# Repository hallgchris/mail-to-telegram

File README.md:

# Mail to Telegram

Idea: Reed switch detects mail entering letterbox. Notify family group chat via Telegram.

Result: Excuse to make a PCB and fiddle with the ESP32 module.

> 🎶 *We just got a letter, we just got a letter...*

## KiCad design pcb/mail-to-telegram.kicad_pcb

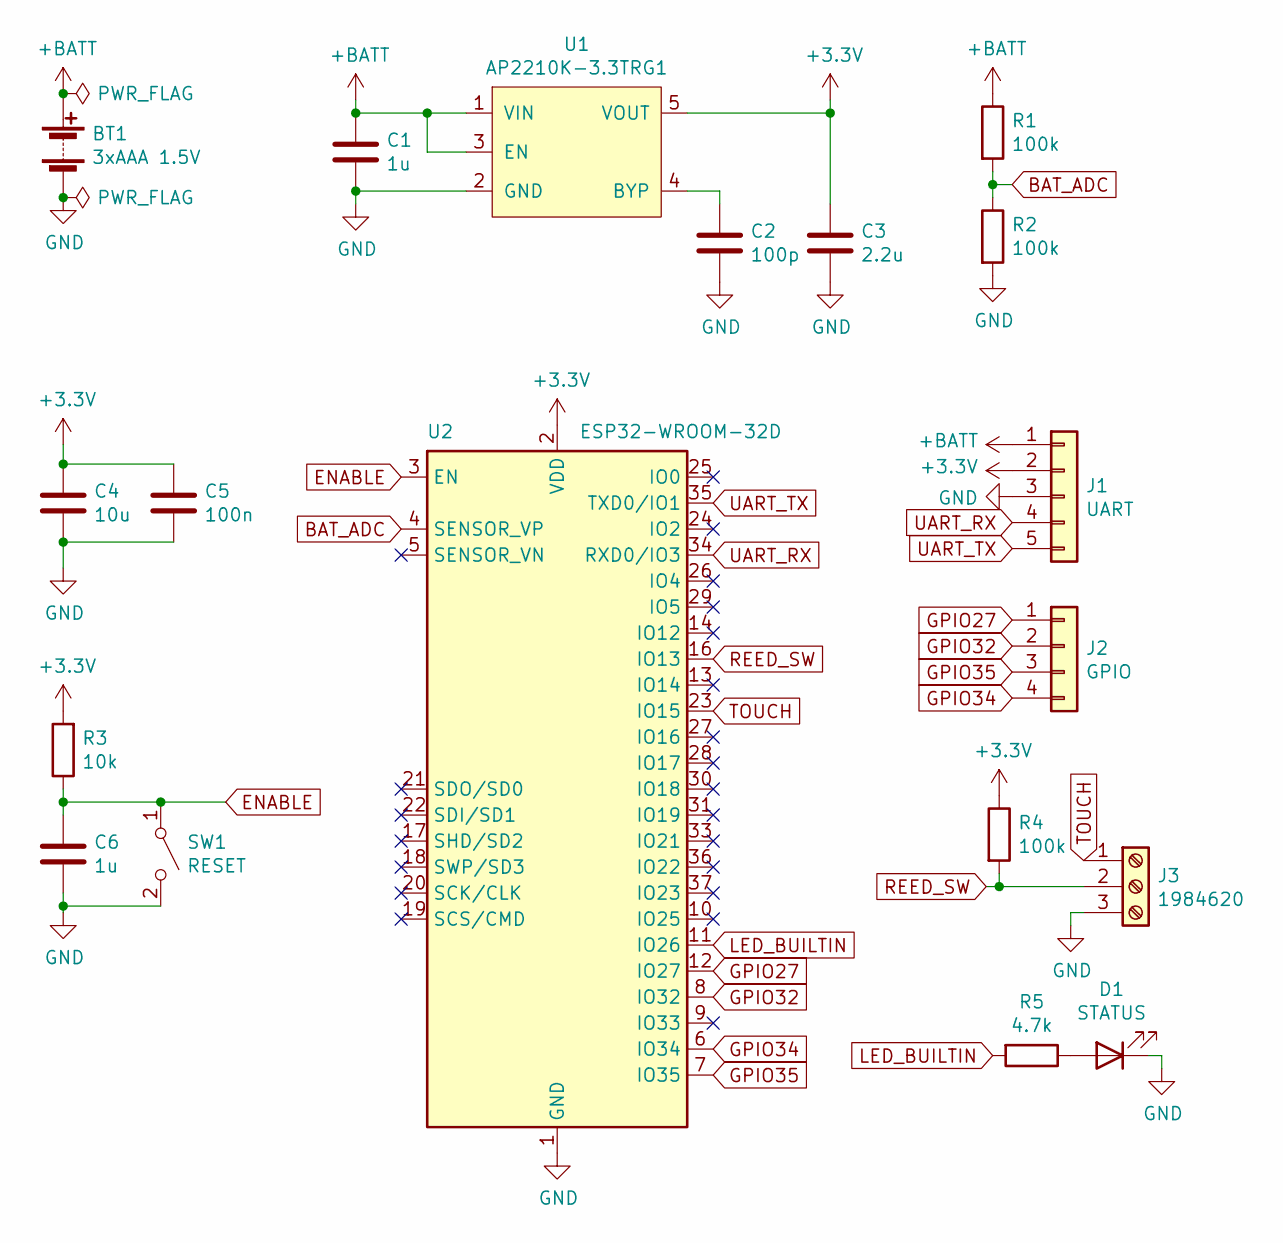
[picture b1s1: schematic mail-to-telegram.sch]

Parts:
BT1: 3xAAA 1.5V; BatteryHolder_Keystone_2479_3xAAA
C1, C6: 1u; C_0603_1608Metric_Pad1.08x0.95mm_HandSolder
C2: 100p; C_0603_1608Metric_Pad1.08x0.95mm_HandSolder
C3: 2.2u; C_0603_1608Metric_Pad1.08x0.95mm_HandSolder
C4: 10u; C_0603_1608Metric_Pad1.08x0.95mm_HandSolder
C5: 100n; C_0603_1608Metric_Pad1.08x0.95mm_HandSolder
D1: STATUS; D_0603_1608Metric_Pad1.05x0.95mm_HandSolder
J1: UART; PinHeader_1x05_P2.54mm_Vertical
J2: GPIO; PinHeader_1x04_P2.54mm_Vertical
J3: 1984620; TerminalBlock_Phoenix_PT-1,5-3-3.5-H_1x03_P3.50mm_Horizontal
R1, R2, R4: 100k; R_0603_1608Metric_Pad0.98x0.95mm_HandSolder
R3: 10k; R_0603_1608Metric_Pad0.98x0.95mm_HandSolder
R5: 4.7k; R_0603_1608Metric_Pad0.98x0.95mm_HandSolder
SW1: RESET; SW_SPST_FSMSM
U1: AP2210K-3.3TRG1; SOT-23-5
U2: ESP32-WROOM-32D; ESP32-WROOM-32

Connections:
+3V3: C3.1, C4.1, C5.1, J1.2, R3.2, R4.1, U1.5 (VOUT), U2.2 (VDD)
+BATT: BT1.1 (+), C1.1, J1.1, R1.1, U1.1 (VIN), U1.3 (EN)
BAT_ADC: R1.2, R2.1, U2.4 (SENSOR_VP)
ENABLE: C6.1, R3.1, SW1.1 (A), U2.3 (EN)
GND: BT1.2 (-), C1.2, C2.2, C3.2, C4.2, C5.2, C6.2, D1.1 (K), J1.3, J3.3, R2.2, SW1.2 (B), U1.2 (GND), U2.1 (GND), U2.15 (GND), U2.38 (GND), U2.39 (GND)
GPIO27: J2.1, U2.12 (IO27)
GPIO32: J2.2, U2.8 (IO32)
GPIO34: J2.4, U2.6 (IO34)
GPIO35: J2.3, U2.7 (IO35)
LED_BUILTIN: R5.2, U2.11 (IO26)
unnamed: C2.1, U1.4 (BYP)
unnamed: D1.2 (A), R5.1
REED_SW: J3.2, R4.2, U2.16 (IO13)
TOUCH: J3.1, U2.23 (IO15)
UART_RX: J1.4, U2.34 (RXD0/IO3)
UART_TX: J1.5, U2.35 (TXD0/IO1)

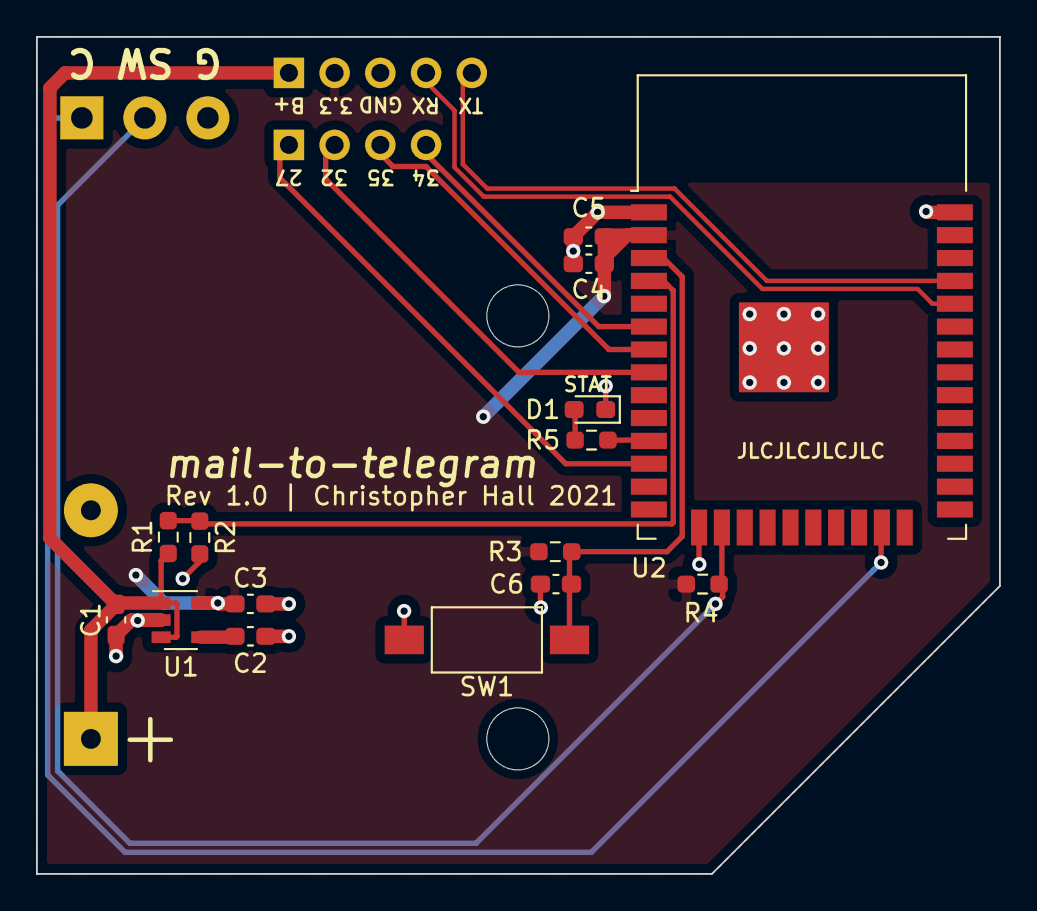
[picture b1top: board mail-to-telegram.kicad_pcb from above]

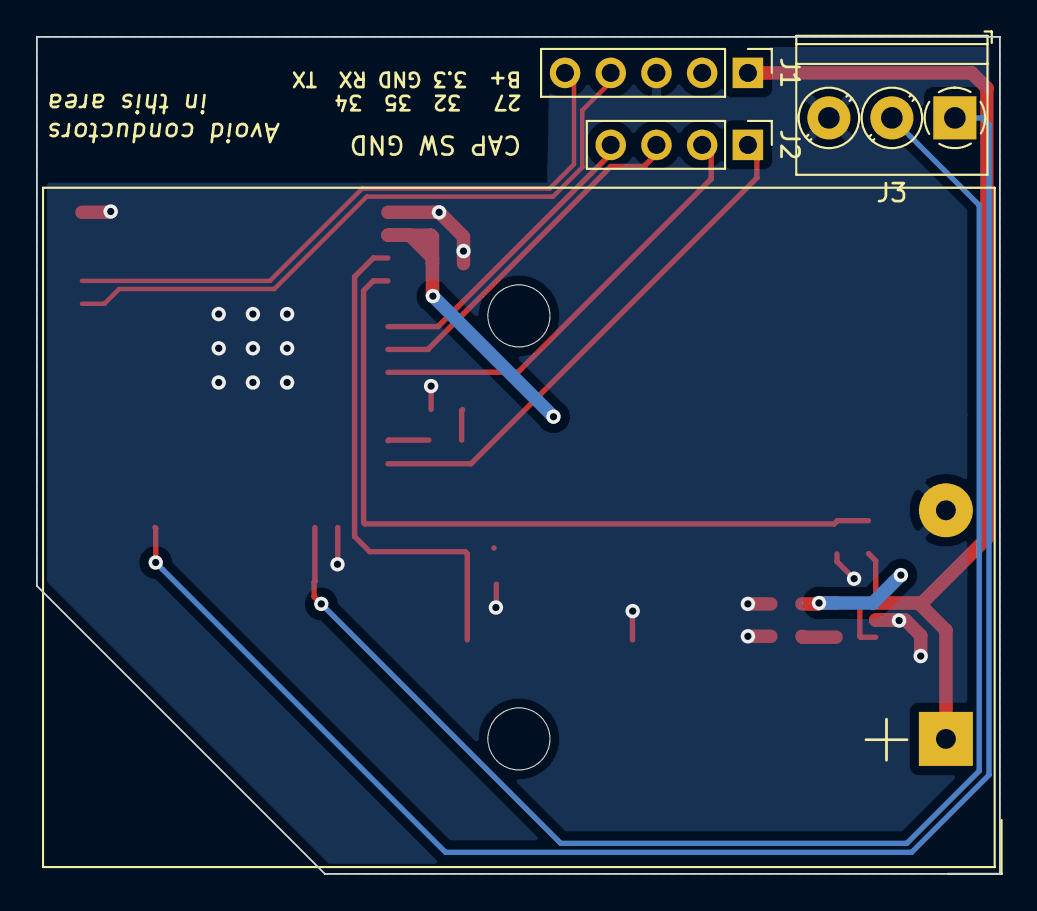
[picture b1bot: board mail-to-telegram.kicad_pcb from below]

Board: 2 copper layers, 53.5 x 46.5 mm, 19 parts (4 on the bottom side), 16 nets.

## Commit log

2021-06-09 pcb: Add v1.0 PCB (no git history whoops)
2021-06-09 firmware: Add very minimal telegram notification
2021-06-09 Add README.md
2021-06-10 fw: Deep sleep while waiting for reed switch trigger
2021-06-11 fw: Read and send battery voltage
2021-06-18 fw: Update pins for PCB (previously for dev board)
2021-06-18 fw: Don't send multiple notifications if switch is held open
2021-06-18 cad: Add initial enclosure design
